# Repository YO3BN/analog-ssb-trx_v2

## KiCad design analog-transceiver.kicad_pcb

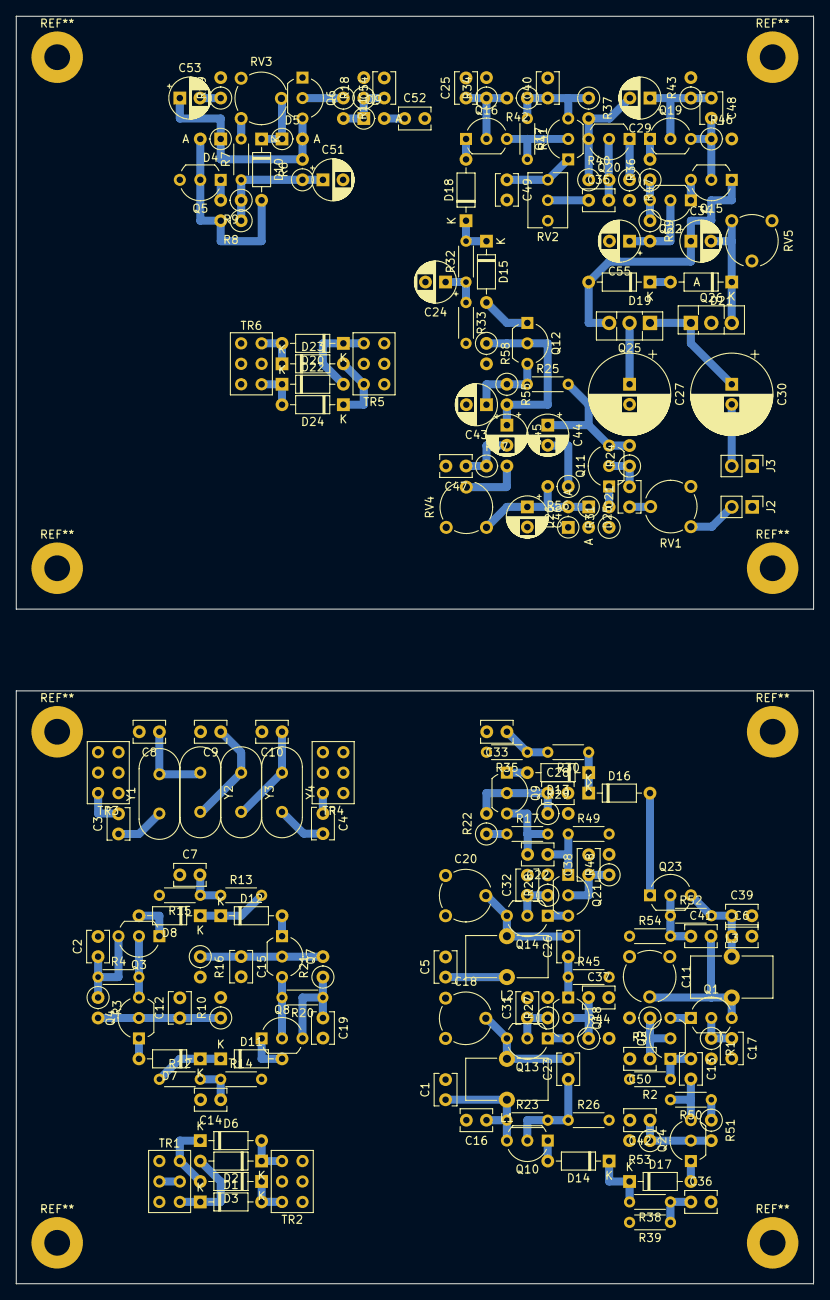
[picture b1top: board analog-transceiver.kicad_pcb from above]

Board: 2 copper layers, 99.1 x 157.5 mm, 186 parts (0 on the bottom side), 104 nets.

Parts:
C1, C2, C5, C6, C7, C12, C13, C14, C15, C16, C17, C19, C21, C22, C23, C25, C26, C28, C31, C32, C33, C35, C36, C37, C38, C39, C40, C41, C42, C50, C52: 100n; C_Disc_D3.8mm_W2.6mm_P2.50mm
C3, C4: 68-82pF; C_Disc_D3.8mm_W2.6mm_P2.50mm
C8, C10: 82-120pF; C_Disc_D3.8mm_W2.6mm_P2.50mm
C9: 100-150pF; C_Disc_D3.8mm_W2.6mm_P2.50mm
C11, C18, C20: CTRIM; Potentiometer_Piher_PT-6-V_Vertical
C24, C29, C51: 10u; CP_Radial_D5.0mm_P2.50mm
C27: 470u; CP_Radial_D10.0mm_P2.50mm
C30: 220u; CP_Radial_D10.0mm_P2.50mm
C34: 1u; CP_Radial_D5.0mm_P2.50mm
C43, C44, C45, C46, C55: CP; CP_Radial_D5.0mm_P2.50mm
C47: C; C_Disc_D3.8mm_W2.6mm_P2.50mm
C48: 820p; C_Disc_D3.8mm_W2.6mm_P2.50mm
C49: 22n?; C_Disc_D3.8mm_W2.6mm_P2.50mm
C53: 4.7u; CP_Radial_D5.0mm_P2.50mm
C54: 10n; C_Disc_D3.8mm_W2.6mm_P2.50mm
D1, D2, D3, D6, D20, D22, D23, D24: BAT41; D_DO-35_SOD27_P7.62mm_Horizontal
D4, D5: 1N4148; D_DO-35_SOD27_P2.54mm_Vertical_AnodeUp
D7, D8, D10, D11, D12, D13, D14, D15, D16, D17, D18, D19, D21: 1N4148; D_DO-35_SOD27_P7.62mm_Horizontal
D9, D25, D26: BAT41; D_DO-35_SOD27_P2.54mm_Vertical_AnodeUp
J2: AF In; PinHeader_1x02_P2.54mm_Vertical
J3: AF Out; PinHeader_1x02_P2.54mm_Vertical
L1, L2, L3: L; L_Toroid_Vertical_L10.0mm_W5.0mm_P5.08mm
Q1, Q3, Q4, Q6, Q7, Q8, Q9, Q10, Q11, Q12, Q13, Q14, Q15, Q16, Q17, Q20, Q22, Q23, Q24: 2N3904; TO-92_Inline_Wide
Q2, Q18, Q21: BF245A; TO-92_Inline_Wide
Q5, Q19: 2N3906; TO-92_Inline_Wide
Q25: BD139; TO-126-3_Vertical
Q26: BD140; TO-126-3_Vertical
R1, R27, R28: 10k; R_Axial_DIN0207_L6.3mm_D2.5mm_P2.54mm_Vertical
R2, R45, R49: 1M; R_Axial_DIN0204_L3.6mm_D1.6mm_P5.08mm_Horizontal
R3, R21, R22, R51: 150k; R_Axial_DIN0207_L6.3mm_D2.5mm_P2.54mm_Vertical
R4, R17, R20, R41, R50: 680; R_Axial_DIN0204_L3.6mm_D1.6mm_P5.08mm_Horizontal
R5, R44, R48: 330; R_Axial_DIN0207_L6.3mm_D2.5mm_P2.54mm_Vertical
R6, R8: 1.5M; R_Axial_DIN0207_L6.3mm_D2.5mm_P2.54mm_Vertical
R7: 2.2k; R_Axial_DIN0204_L3.6mm_D1.6mm_P5.08mm_Horizontal
R9: 47k; R_Axial_DIN0207_L6.3mm_D2.5mm_P2.54mm_Vertical
R10, R16, R29, R53: 56k; R_Axial_DIN0207_L6.3mm_D2.5mm_P2.54mm_Vertical
R11: 2.2k; R_Axial_DIN0207_L6.3mm_D2.5mm_P2.54mm_Vertical
R12, R13, R30, R32, R38: 47; R_Axial_DIN0204_L3.6mm_D1.6mm_P5.08mm_Horizontal
R14, R15, R33, R35, R39: 390; R_Axial_DIN0204_L3.6mm_D1.6mm_P5.08mm_Horizontal
R18: 100k; R_Axial_DIN0207_L6.3mm_D2.5mm_P2.54mm_Vertical
R19, R34, R42: 0; R_Axial_DIN0207_L6.3mm_D2.5mm_P2.54mm_Vertical
R23, R26, R52, R54: R; R_Axial_DIN0204_L3.6mm_D1.6mm_P5.08mm_Horizontal
R24, R40, R43: 330k; R_Axial_DIN0207_L6.3mm_D2.5mm_P2.54mm_Vertical
R25: 2k2; R_Axial_DIN0204_L3.6mm_D1.6mm_P5.08mm_Horizontal
R31, R36, R47: 220; R_Axial_DIN0207_L6.3mm_D2.5mm_P2.54mm_Vertical
R37, R46: 2k2; R_Axial_DIN0207_L6.3mm_D2.5mm_P2.54mm_Vertical
R55, R56, R57, R58, R59: R; R_Axial_DIN0207_L6.3mm_D2.5mm_P2.54mm_Vertical
RV1: 10K; Potentiometer_Piher_PT-6-V_Vertical
RV2: 0; Potentiometer_Vishay_T73XW_Horizontal
RV3, RV5: 5k; Potentiometer_Piher_PT-6-V_Vertical
RV4: R_POT; Potentiometer_Piher_PT-6-V_Vertical
TR1, TR2, TR5, TR6: 3x7 43-binocular; SW_NKK_G1xJP
TR3: 2:5; SW_NKK_G1xJP
TR4: 5:2; SW_NKK_G1xJP
Y1, Y2, Y3, Y4: 10MHz; Crystal_HC49-U_Vertical

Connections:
+RX: C1.1, C2.1, C5.1, C16.1, C40.1, C51.1, L1.1, L2.1, Q3.3, Q10.3, Q17.3, Q22.3, R3.1, R4.1, R6.1, R7.1, R8.1, R9.1, R17.1, R22.1, R23.1, R36.1, R37.1, R41.1, R42.1, R59.1
+TX: C6.1, C19.1, C39.1, C43.1, L3.1, Q8.3, Q12.3, Q23.3, R20.1, R21.1, R25.1, R50.1, R51.1, R52.2, R55.1, RV1.1
GND: C1.2, C2.2, C5.2, C6.2, C8.2, C9.2, C10.2, C11.1, C11.3, C12.2, C15.2, C16.2, C17.2, C18.1, C18.3, C19.2, C20.1, C20.3, C25.2, C27.2, C28.2, C31.2, C32.2, C37.2, C38.2, C39.2, C40.2, C42.2, C43.2, C46.2, C47.2, C49.2, C50.2, C51.2, C54.2, C55.2, D25.2, D26.1, J2.1, J3.1, Q5.3, Q6.1, Q26.2, R2.2, R5.2, R10.2, R14.2, R15.2, R16.2, R18.2, R19.2, R26.2, R29.2, R31.1, R33.2, R34.2, R35.2, R39.2, R44.2, R45.2, R46.2, R47.2, R48.2, R49.2, R53.2, R54.1, R58.2, RV2.1, RV3.3, RV4.3, RV5.2, RV5.3, TR1.1, TR2.2, TR2.3, TR2.5, TR3.3, TR3.4, TR4.3, TR4.4, TR5.1, TR6.2, TR6.3, TR6.5
IFGain: Q5.1, R9.2, R27.2, R28.2
unnamed: C3.1, Y1.1
unnamed: C3.2, TR3.6
unnamed: C4.1, TR4.6
unnamed: C4.2, Y4.2
unnamed: C7.1, TR3.1
unnamed: C7.2, R13.1, R15.1
unnamed: C8.1, Y1.2, Y2.1
unnamed: C9.1, Y2.2, Y3.1
unnamed: C10.1, Y3.2, Y4.1
unnamed: C11.2, C41.2, L3.2, Q1.3
unnamed: C12.1, Q4.2, R3.2, R10.1
unnamed: C13.1, Q2.1, R2.1
unnamed: C13.2, Q24.3, R50.2
unnamed: C14.1, R12.2, R14.1
unnamed: C14.2, TR1.5
unnamed: C15.1, Q7.2, R16.1, R21.2
unnamed: C17.1, Q1.2, R1.1
unnamed: C18.2, C23.2, L1.2, Q13.3
unnamed: C20.2, C26.2, L2.2, Q14.3
unnamed: C21.1, RV1.2
unnamed: C21.2, Q11.2, R24.1
unnamed: C22.1, Q21.1, R49.1
unnamed: C22.2, Q9.3, R17.2
unnamed: C23.1, Q10.2, R23.2, R26.1
unnamed: C24.1, R32.1, R33.1
unnamed: C24.2, TR5.5
unnamed: C25.1, Q16.2, R34.1, R42.2
unnamed: C26.1, Q18.1, R45.1
unnamed: C27.1, Q15.3, Q22.1, Q25.2
unnamed: C28.1, Q9.2, R22.2, R29.1
unnamed: C29.1, C48.1, Q19.2, R43.1
unnamed: C29.2, Q20.3, R37.2, R40.1
unnamed: C30.1, Q25.1, Q26.1, R43.2
unnamed: C30.2, J3.2
unnamed: C31.1, Q13.2, R27.1
unnamed: C32.1, Q14.2, R28.1
unnamed: C33.1, R30.2, R35.1
unnamed: C33.2, TR4.1
unnamed: C34.1, D19.2, Q15.1, Q25.3
unnamed: C34.2, D21.1, Q26.3, RV5.1
unnamed: C35.1, RV2.2
unnamed: C35.2, Q20.2, R40.2
unnamed: C36.1, R38.1, R39.1
unnamed: C36.2, TR5.3
unnamed: C37.1, Q18.2, R44.1
unnamed: C38.1, Q21.2, R48.1
unnamed: C41.1, Q23.2, R52.1, R54.2
unnamed: C42.1, Q24.2, R51.2, R53.1
unnamed: C44.1, Q11.3, R24.2, R25.2
unnamed: C44.2, R56.1
unnamed: C45.1, Q12.2, R55.2, R58.1
unnamed: C45.2, C47.1, R57.1
unnamed: C46.1, D25.1, D26.2, R56.2, RV4.1
unnamed: C48.2, Q15.2, Q19.3, R46.1
unnamed: C49.1, Q17.1, RV2.3
unnamed: C50.1, Q2.2, R5.1
unnamed: C52.1, D9.2
unnamed: C53.1, D4.1, D5.2, Q6.3, R6.2
unnamed: C53.2, R19.1
unnamed: C54.1, D9.1, R11.2, R18.1
unnamed: C55.1, Q22.2, R59.2
unnamed: D1.1, D2.2, TR1.4
unnamed: D1.2, D3.1, TR2.6
unnamed: D2.1, D6.2, TR2.4
unnamed: D3.2, D6.1, TR1.6
unnamed: D7.2, Q4.1
unnamed: D8.2, Q3.1
unnamed: D5.1, D10.1, RV3.2
unnamed: D4.2, D10.2, Q5.2, R8.2
unnamed: D7.1, D11.1, R12.1
unnamed: D11.2, Q8.1
unnamed: D8.1, D12.1, R13.2
unnamed: D12.2, Q7.1
unnamed: D13.1, D16.1, R30.1
unnamed: D13.2, Q9.1
unnamed: D14.1, D17.1, R38.2
unnamed: D14.2, Q10.1
unnamed: D15.1, D18.1, R32.2
unnamed: D15.2, Q12.1
unnamed: D16.2, Q23.1
unnamed: D17.2, Q24.1
unnamed: D18.2, Q16.1
unnamed: D19.1, D21.2
unnamed: D20.1, D22.2, TR5.4
unnamed: D20.2, D23.1, TR6.6
unnamed: D22.1, D24.2, TR6.4
unnamed: D23.2, D24.1, TR5.6
unnamed: J2.2, RV1.3
unnamed: Q1.1, Q2.3
unnamed: Q3.2, Q4.3, R4.2
unnamed: Q6.2, R11.1
unnamed: Q7.3, Q8.2, R20.2
unnamed: Q11.1, R31.2
unnamed: Q13.1, Q18.3
unnamed: Q14.1, Q21.3
unnamed: Q16.3, Q17.2, R41.2
unnamed: Q19.1, R36.2
unnamed: Q20.1, R47.1
unnamed: R7.2, RV3.1
unnamed: R57.2, RV4.2

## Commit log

2022-10-12 First commit.
2022-10-19 Added Bridged Tee diplexer after diode DBM (10.7MHz@50ohms).
